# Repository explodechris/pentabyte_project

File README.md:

# Pentabyte — Voice AI Coach

A voice-first AI coaching application for career and academic goal clarification. The project consists of two components: a **web application** (software) and an **ESP32-based hardware prototype** (physical device).

---

## ESP32 Hardware Integration

The repository includes firmware at [pentabyte electronics/Pentabyte/src/main.cpp](pentabyte%20electronics/Pentabyte/src/main.cpp) that connects your physical device to the web backend over Wi-Fi.

### Supported hardware path

- Press and hold button (GPIO4) to record from I2S microphone
- Release button to send WAV audio to backend (`/api/esp32/turn`)
- Backend runs STT + coaching + TTS
- ESP32 receives MP3 response and plays it via I2S speaker

### Pin mapping used in firmware

- OLED SSD1351 (VSPI): MOSI=23, CLK=18, CS=5, DC=21, RST=22
- I2S microphone: SCK=16, WS=17, SD=34
- I2S speaker DAC: BCLK=26, LRC=27, DOUT=25
- SD card (HSPI): SCK=14, MISO=19, MOSI=13, CS=15
- Push button: GPIO4 (`INPUT_PULLUP`, active low)

### Configure firmware

Edit these constants in [pentabyte electronics/Pentabyte/src/main.cpp](pentabyte%20electronics/Pentabyte/src/main.cpp):

- `WIFI_SSID`
- `WIFI_PASS`
- `SERVER_URL` (your computer's LAN IP + Next.js port, for example `http://192.168.1.42:3000`)

Important: ESP32 and your computer must be on the same Wi-Fi network.

### Backend requirements

- `GEMINI_API_KEY` is required
- `ELEVENLABS_API_KEY` is required for hardware audio playback (the ESP32 endpoint returns MP3)
- Start server with `npm run dev`

### Flash firmware (PlatformIO)

From [pentabyte electronics/Pentabyte](pentabyte%20electronics/Pentabyte):

```bash
pio run -t upload
pio device monitor -b 115200
```

If `pio` is missing, install PlatformIO Core first:

```bash
python3 -m pip install -U platformio
```

### Quick test checklist

1. Start Next.js server and confirm it is reachable from another device on LAN.
2. Power ESP32 and confirm serial log shows Wi-Fi connected and session started.
3. Hold button while speaking, then release.
4. Confirm serial log shows audio upload and MP3 bytes received.
5. Confirm response plays from speaker and OLED state transitions (`REC` -> `THINKING...` -> `SPEAKING...`).

## Project Structure

```
pentabyte_project/
├── website/          # Next.js web application (AI coaching backend + frontend)
└── hardware/         # ESP32 hardware prototype (audio capture + playback device)
```

---

## Components

### Website — AI Coaching Web App

A browser-based, voice-driven coaching tool. The user selects personality traits that shape the coaching style, then holds a push-to-talk button to speak. Audio is transcribed by the Gemini API, processed by an LLM coaching engine, and the AI response is synthesized back to speech via ElevenLabs.

**Stack:** Next.js 14, TypeScript, Tailwind CSS, Gemini API (STT + LLM), ElevenLabs (TTS), Vercel

→ See [`website/README.md`](website/README.md) for setup and deployment instructions.

---

### Hardware — ESP32 Audio Prototype

A standalone embedded prototype built around an ESP32 microcontroller. The device captures audio via an I2S MEMS microphone (push-to-talk, hold button), encodes and stores it as a WAV file on an SD card, then plays it back through an I2S DAC and speaker. A 128×128 OLED display provides visual state feedback (idle, recording, playback).

This prototype was developed in parallel with the web application as a proof-of-concept for a self-contained physical coaching device, prior to hardware–software integration.

**Hardware:** ESP32, SSD1351 OLED display, I2S MEMS microphone, I2S DAC/speaker, SD card
**Firmware:** PlatformIO / Arduino framework (C++)
**PCB:** Custom board designed in Eagle (KiCad-compatible export available)

→ See [`hardware/README.md`](hardware/README.md) for build and instructions.

---

## Quick Start

**Web app:**
```bash
cd website
npm install
# add .env.local (see website/README.md)
npm run dev
```

**Hardware firmware:**
```bash
# Open hardware/Firmware/ in PlatformIO
# Connect ESP32 via USB
pio run --target upload
```

---

## Status

| Component | Status |
|-----------|--------|
| Web app | Functional — deployable to Vercel |
| Hardware firmware | Prototype — standalone audio record/playback working |
| Hardware–software integration | Not yet implemented |

---

## Team

[Sinem Unlu](https://github.com/sinem-unlu-sf)\
[Cristian Rosca](https://github.com/explodechris)\
Enkh-Oyun Tsend-Ayush\
Rida Habib\
Muhammad Habib

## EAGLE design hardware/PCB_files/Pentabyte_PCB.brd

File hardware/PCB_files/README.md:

# PCB Design Files

Custom PCB for the Pentabyte ESP32 hardware prototype, designed in Autodesk Eagle.

---

## Files

| File | Description |
|------|-------------|
| `Pentabyte_PCB.brd` | Eagle board layout — copper layers, component placement, routing |
| `Pentabyte_PCB_schematic.sch` | Eagle schematic — full circuit diagram |

---

## Opening the Files

**Eagle (Autodesk):**
- Open `.brd` in Eagle for the board layout
- Open `.sch` in Eagle for the schematic
- Eagle 7.x or later recommended

**KiCad (alternative):**
- Use the [Eagle-to-KiCad importer](https://docs.kicad.org/7.0/en/pcbnew/pcbnew.html#importing_eagle_files) built into KiCad 5.1+
- File → Import → Eagle Project

---

## Design Notes

The PCB integrates the core components of the prototype onto a single board:

- **ESP32** (main microcontroller)
- **SSD1351 OLED display** connector — VSPI bus (MOSI, CLK, CS, DC, RST)
- **SD card slot** — HSPI bus (separate from display SPI to avoid bus contention)
- **I2S MEMS microphone** footprint — I2S port 1
- **I2S DAC / speaker amplifier** connector — I2S port 0
- **Push button** — GPIO4 with pull-up

Refer to [`../Firmware/README.md`](../Firmware/README.md) for the full pin assignment table.

---

## Fabrication

Standard 2-layer PCB. To order:

1. Generate Gerber files from the `.brd` file (Eagle: File → CAM Processor → Gerber)
2. Upload Gerbers to your preferred PCB manufacturer (JLCPCB, PCBWay, OSH Park, etc.)
3. Standard 1.6mm FR4, 1oz copper, HASL or ENIG finish

---

## Prototype Photos

See the images in [`../`](../) for the breadboard prototype and assembled hardware.

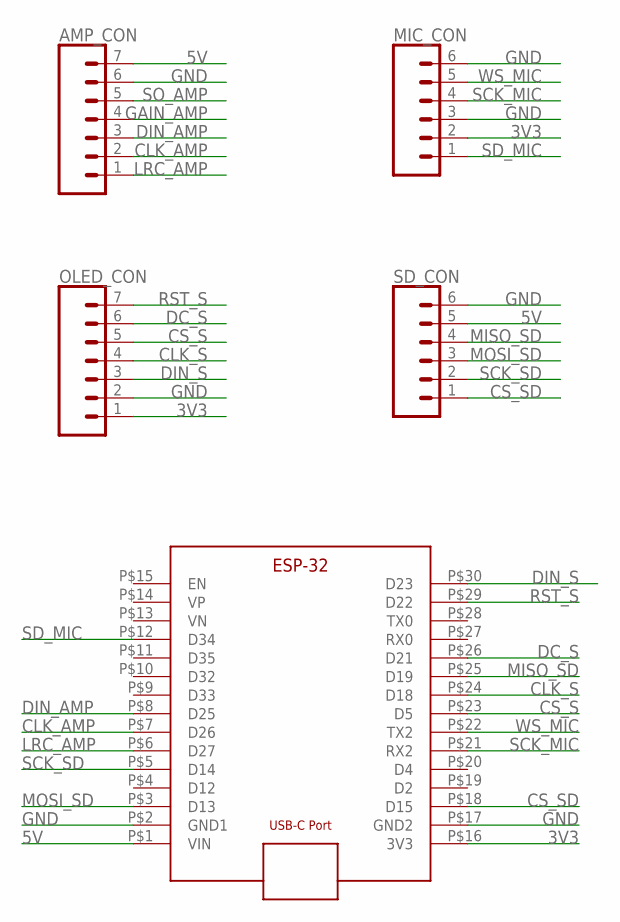
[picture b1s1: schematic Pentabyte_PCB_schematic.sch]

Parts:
AMP_CON: CONN_07; 1X07
MIC_CON: CONN_06SILK_FEMALE_PTH; 1X06
OLED_CON: CONN_07; 1X07
SD_CON: CONN_06SILK_FEMALE_PTH; 1X06
U$1: ESP-WROOM-32_DEVKITESP-WROOM-32; ESP-WROOM-32

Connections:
3V3: MIC_CON.2, OLED_CON.1, U$1.P$16 (3V3)
5V: AMP_CON.7, SD_CON.5, U$1.P$1 (VIN)
CLK_AMP: AMP_CON.2, U$1.P$7 (D26)
CLK_S: OLED_CON.4, U$1.P$24 (D18)
CS_S: OLED_CON.5, U$1.P$23 (D5)
CS_SD: SD_CON.1, U$1.P$18 (D15)
DC_S: OLED_CON.6, U$1.P$26 (D21)
DIN_AMP: AMP_CON.3, U$1.P$8 (D25)
DIN_S: OLED_CON.3, U$1.P$30 (D23)
GAIN_AMP: AMP_CON.4
GND: AMP_CON.6, MIC_CON.3, MIC_CON.6, OLED_CON.2, SD_CON.6, U$1.P$2 (GND1), U$1.P$17 (GND2)
LRC_AMP: AMP_CON.1, U$1.P$6 (D27)
MISO_SD: SD_CON.4, U$1.P$25 (D19)
MOSI_SD: SD_CON.3, U$1.P$3 (D13)
RST_S: OLED_CON.7, U$1.P$29 (D22)
SCK_MIC: MIC_CON.4, U$1.P$21 (RX2)
SCK_SD: SD_CON.2, U$1.P$5 (D14)
SD_MIC: MIC_CON.1, U$1.P$12 (D34)
SO_AMP: AMP_CON.5
WS_MIC: MIC_CON.5, U$1.P$22 (TX2)

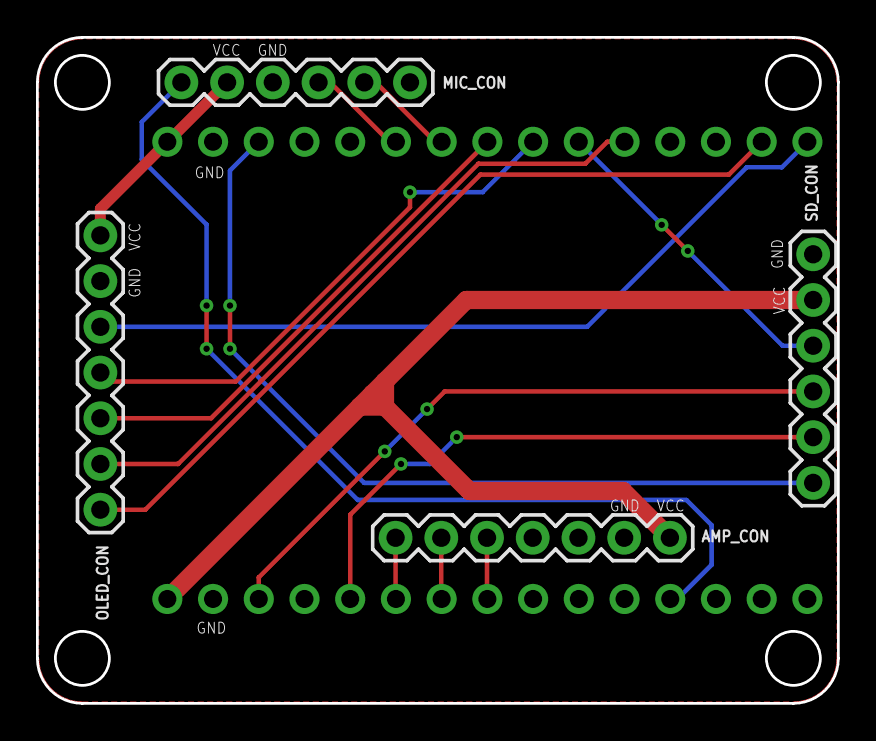
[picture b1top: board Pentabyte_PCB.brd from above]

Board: 2 copper layers, 44.5 x 37.0 mm, 5 parts (1 on the bottom side), 18 nets.

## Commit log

2026-04-05 Upload hardware files
2026-04-05 file organization
2026-04-05 READMEs added
2026-04-20 keys

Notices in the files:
parts and their libraries:
SparkFun-Connectors: Licensing: Creative Commons ShareAlike 4.0 International - https://creativecommons.org/licenses/by-sa/4.0
